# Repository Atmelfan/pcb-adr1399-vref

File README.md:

# pcb-adr1399-vref

**NOTICE** - The main branch is probably not production ready. Check out [Releases](https://github.com/Atmelfan/pcb-adr1399-vref/releases) for finished revisions.

A simple 10 V voltage reference based on [ADR1399](https://www.analog.com/en/products/adr1399.html) from Analog Devices.

# Schematic

Check out [Releases](https://github.com/Atmelfan/pcb-adr1399-vref/releases) for revision schematics and materials.

# Tools used
* Schematic & Layout - [KiCad 6](https://www.kicad.org/)
* Assembly - [FreeCad 0.19](https://www.freecadweb.org/)

# License
This work is licensed under [CERN Open Hardware Licence Version 2 - Strongly Reciprocal](https://www.ohwr.org/project/cernohl/wikis/Documents/CERN-OHL-version-2).

See [LICENSE.txt](LICENSE.txt) for full text.

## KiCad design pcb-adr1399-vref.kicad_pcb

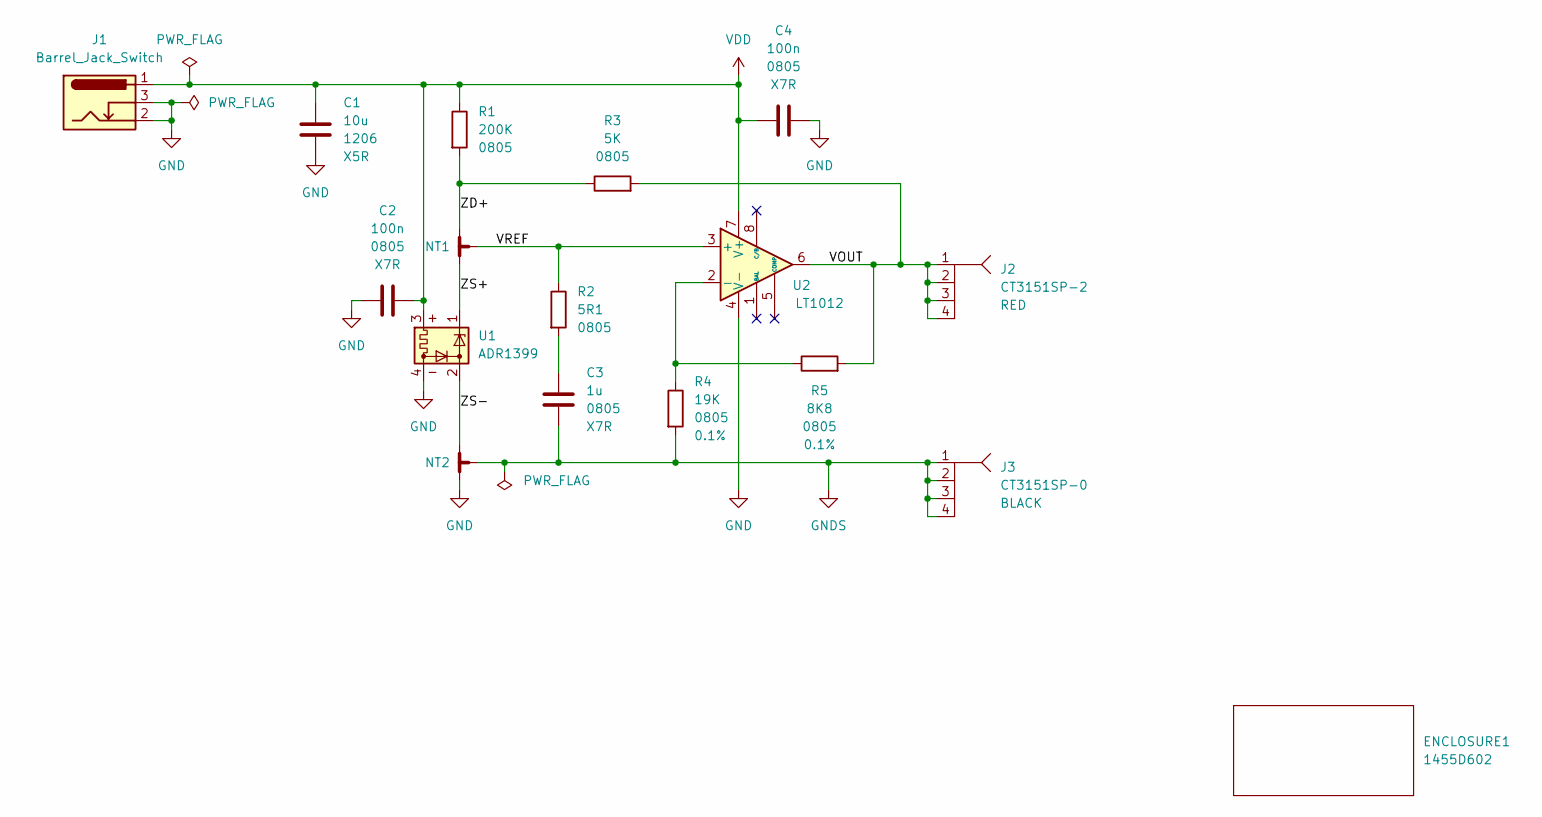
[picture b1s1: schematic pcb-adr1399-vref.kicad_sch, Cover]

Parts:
C1: 10u; C_1206_3216Metric_Pad1.33x1.80mm_HandSolder
C2, C4: 100n; C_0805_2012Metric_Pad1.18x1.45mm_HandSolder
C3: 1u; C_0805_2012Metric_Pad1.18x1.45mm_HandSolder
ENCLOSURE1: 1455D602; mpn 1455D602; digikey# HM1354-ND
J1: Barrel_Jack_Switch; 54-00130; mpn 54-00130; digikey# 839-1513-ND
J2: CT3151SP-2; CT3151SP; mpn CT3151SP-2; digikey# BKCT3151SP-2-ND
J3: CT3151SP-0; CT3151SP; mpn CT3151SP-0; digikey# BKCT3151SP-0-ND
NT1, NT2: NetTie_3_Tee; NetTie-3_SMD_Pad0.5mm
R1: 200K; R_0805_2012Metric_Pad1.20x1.40mm_HandSolder
R2: 5R1; R_0805_2012Metric_Pad1.20x1.40mm_HandSolder
R3: 5K; R_0805_2012Metric_Pad1.20x1.40mm_HandSolder
R4: 19K; R_0805_2012Metric_Pad1.20x1.40mm_HandSolder; Tolerance 0.1%
R5: 8K8; R_0805_2012Metric_Pad1.20x1.40mm_HandSolder; Tolerance 0.1%
U1: ADR1399; Analog_TO-46-4_ThermalShield
U2: LT1012; SO-8_3.9x4.9mm_P1.27mm; mpn LT1012ACS8#PBF; digikey# LT1012ACS8#PBF-ND

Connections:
/VOUT: J2.1, J2.2, J2.3, J2.4, R3.2, R5.2, U2.6
/VREF: NT1.3, R2.1, U2.3 (+)
/ZD+: NT1.2, R1.2, R3.1
/ZS+: NT1.1, U1.1
/ZS-: NT2.2, U1.2
GND: C1.2, C2.2, C4.2, J1.2, J1.3, NT2.1, U1.4, U2.4 (V-)
GNDS: C3.2, J3.1, J3.2, J3.3, J3.4, NT2.3, R4.2
unnamed: C3.1, R2.2
unnamed: R4.1, R5.1, U2.2 (-)
VDD: C1.1, C2.1, C4.1, J1.1, R1.1, U1.3, U2.7 (V+)

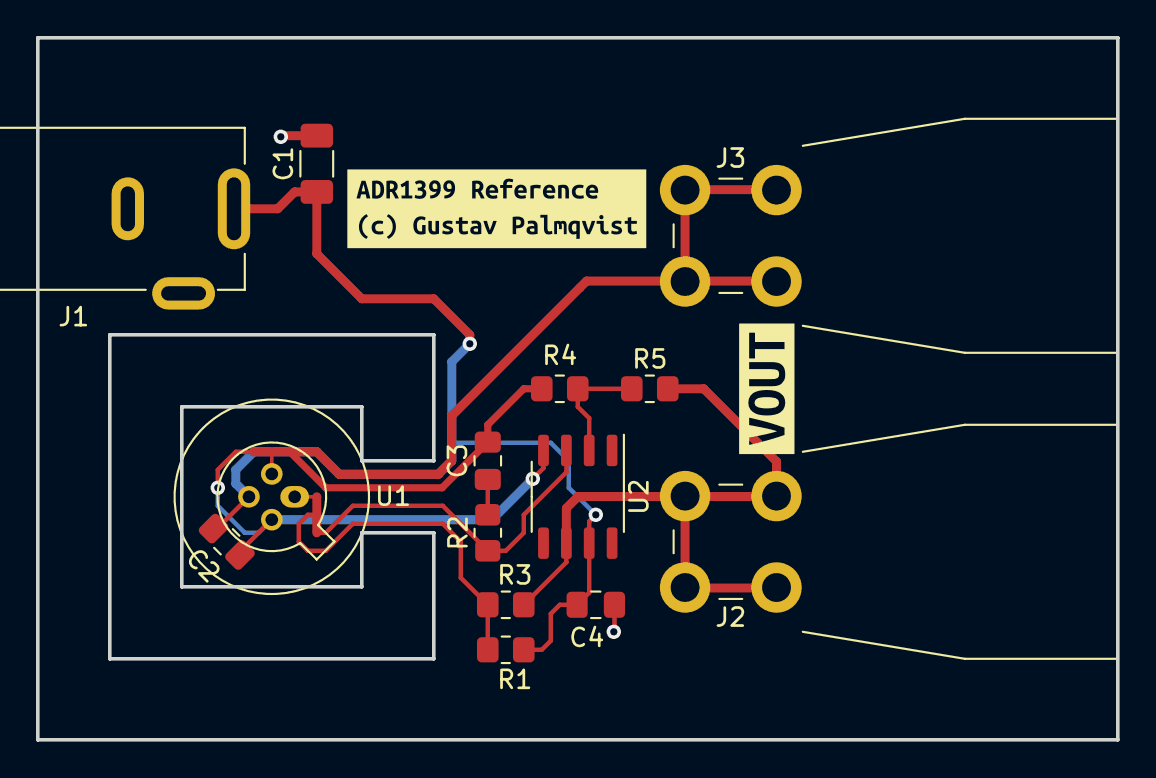
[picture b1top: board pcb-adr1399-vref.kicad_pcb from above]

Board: 2 copper layers, 60.0 x 39.0 mm, 18 parts (0 on the bottom side), 10 nets.

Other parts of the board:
kibuzzard-61E8B62B: G***; kibuzzard-61E8B62B
kibuzzard-61FB27BC: G***; kibuzzard-61FB27BC

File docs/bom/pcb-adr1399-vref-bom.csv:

References;Description;Part;Value;Qty;size;type;digikey#;mpn;color;tolerance
C2 C4;Unpolarized capacitor;C;100n;2;0805;X7R;;;;
C3;Unpolarized capacitor;C;1u;1;0805;X7R;;;;
C1;Unpolarized capacitor;C;10u;1;1206;X5R;;;;
ENCLOSURE1;"Box Metal, Aluminum; Plastic Natural End Panel(s) 2.362"" L x 1.673"" W (60.00mm x 42.50mm) X 0.906"" (23.00mm)";1455D602;1455D602;1;;;HM1354-ND;1455D602;;
J1;DC Barrel Jack with an internal switch;Barrel_Jack_Switch;Barrel_Jack_Switch;1;;;839-1513-ND;54-00130;;
J3;Banana Jack Connector Standard Banana Solder Red;CT3151SP-0;CT3151SP-0;1;;;BKCT3151SP-0-ND;CT3151SP-0;BLACK;
J2;Banana Jack Connector Standard Banana Solder Red;CT3151SP-2;CT3151SP-2;1;;;BKCT3151SP-2-ND;CT3151SP-2;RED;
R2;Resistor;R;5R1;1;0805;;;;;
R3;Resistor;R;5K;1;0805;;;;;
R5;Resistor;R;8K8;1;0805;;;;;0.1%
R4;Resistor;R;19K;1;0805;;;;;0.1%
R1;Resistor;R;200K;1;0805;;;;;
U1;Oven-Compensated, Buried Zener, 7.05 V Voltage Reference;ADR1399;ADR1399;1;;;;;;
U2;Single Picoamp Input Current, Microvolt Offset, Low Noise Op Amp, DIP-8/SOIC-8/TO-5-8;LT1012;LT1012;1;;;LT1012ACS8#PBF-ND;LT1012ACS8#PBF;;

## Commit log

2022-01-21 First revision
2022-02-03 Ordered P1B
2022-02-03 Fix CI/CD
2022-02-03 Fixed submodule
2022-02-03 Ignore kibout outputs
2022-02-03 Checkout submodules
2022-02-03 Again
2022-02-03 Duplicated name
2022-02-03 Test
2022-02-03 asdfg
2022-02-03 Pages
2022-02-03 srth
2022-02-03 Initial gh-pages commit
2022-02-03 Deploying to gh-pages from @ Atmelfan/pcb-adr1399-vref@9dd6aa1a1aac616bf5fba06f109b5dc87cc3ff95 🚀
2022-02-03 erfgbeth
2022-02-03 Deploy on release only
2022-02-03 Add rsync
2022-02-03 Deploying to gh-pages from @ Atmelfan/pcb-adr1399-vref@42d1b3c6a442e3b5243eb42099689c064005cf90 🚀
2022-02-03 Removed step file
2022-02-03 Release schematics
2022-02-03 Deploying to gh-pages from @ Atmelfan/pcb-adr1399-vref@9785d729a6f2eb738e8dea6960c3aa0cc603fe6b 🚀
2022-02-04 test pr action
2022-02-04 trigger
2022-02-04 4t3rt
2022-02-04 Remove pull request workflow
2022-02-04 Updated release workflow
2022-02-04 Deploying to gh-pages from @ Atmelfan/pcb-adr1399-vref@a7292277256407f949378d21e8d5ccdddb0bd8f4 🚀
2022-02-07 Generate docs if Preflight checks are ok
2023-02-03 Kicad 7

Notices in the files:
pcb-adr1399-vref.kicad_sch:
Licensed under CERN-OHL-S version 2
